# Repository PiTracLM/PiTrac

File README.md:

**Introduction to PiTrac:**

- [Introduction](#introducing-pitrac)
  - [Project Page](#project-page)
- [PiTrac - Start Here](#getting-started)
- [PiTrac - Setup and Configuration](#setup-and-configuration)
- [PiTrac - Licensing](#licensing)
- [PiTrac - Join the Discord](#join-the-discord)

## Introducing PiTrac
Introducing [PiTrac](https://hackaday.io/project/195042-pitrac-the-diy-golf-launch-monitor) \- the world’s first (free\!) open-source golf launch monitor (as far as we know). 

PiTrac uses low-cost Raspberry Pi(\*) computers and cameras to determine golf ball launch speed, angles and spin in three dimensions.  PiTrac interfaces with both GSPro and E6/TruGolf simulators, and its output is also accessible on a stand-alone web-based app.  \[We’ve reached out to 2k/TopGolf, but no response yet.\]

PiTrac uses off-the-shelf hardware, and includes a [parts list](https://docs.pitrac.org/hardware/parts-list/) with links to potential suppliers.  The only custom part is a small printed circuit board.  The fabrication instructions for that PCB are included in the open-source distribution and it can be manufactured for a few dollars.  The two Pi computers and cameras are the most expensive parts, and cost around $250 in total.

PiTrac is not a commercial product for sale–the full design is being released as open source on GitHub for folks to build themselves.  It’s not easy, but if you’re handy with a soldering iron, can figure out how to 3D print the parts, and are willing to burrow into the Linux operating system to compile and install software, you should be able to create your own PiTrac\!  

We are hoping that we can inspire a community of developers to help test and continue PiTrac’s development.  This is a really immature project right now.  The basic features usually work reliably, but the current release is a bit dodgy.  We’re looking for folks to try building their own PiTracs and help us improve the documentation and design to make it easier for other people to do the same.

## Project Page
Please visit our [project page](https://hackaday.io/project/195042-pitrac-the-diy-golf-launch-monitor) and also our YouTube channel [here](https://www.youtube.com/@PiTrac) for more details and videos.  The [GitHub repository](https://github.com/pitraclm/PiTrac) is in the works and already has the 3D printed part designs, the hardware design and initial software documentation.  If you’re interested in more of the details and some of PiTrac’s development history, please look through the [project logs](https://hackaday.io/project/195042-pitrac-the-diy-golf-launch-monitor#menu-logs).  

Finally, any help at our [support page](https://ko-fi.com/Pitrac) would be appreciated to continue this work and complete the release process.

(\*) Raspberry Pi is a trademark of Raspberry Pi Ltd.  The PiTrac project is not endorsed, sponsored by or associated with Raspberry Pi or Raspberry Pi products or services.

## [Getting Started](https://docs.pitrac.org/build-guide/)
The process of building your own PiTrac DIY Launch Monitor is described here at a high level. There are several more-detailed instruction documents elsewhere in the PiTrac repository that are referred to below for various sub-assemblies and tasks like compiling the code and preparing the build environment.

## [Setup and Configuration](https://docs.pitrac.org/software/pi-setup/)
The instructions which are targeted toward getting setup on a step-by-step basis. These instructions start with a Raspberry Pi with nothing on it, and are meant to describe all the steps to get from that point to a working, compiled version of PiTrac.  A single RPi5 is currently our recommended path for everyone, however the path to stereoscopic vision may require two (if/when we head down that path).

## Licensing

PiTrac is distributed under two separate licenses.

The software, documentation, and hardware designs are licensed under the GNU General Public License v2.0. See [`LICENSE`](LICENSE).

PiTrac's trained machine-learning models are not covered by the GPL. They are licensed separately under [`LICENSE.MODEL.md`](LICENSE.MODEL.md), which sets out its own scope and terms. Read it before you use them.

For licensing questions, get in touch through https://github.com/PiTracLM.

## [Join the Discord](https://discord.gg/gMQcBBQYHT)
The PiTrac discord is where you can get help or show off your PiTrac build, discuss features and get to know other PiTrac builders. PiTrac is still a new project, so the Discord is a way to clear up any fuzzy parts of the initial ecosystem. Click the link above or copy this invite link in Discord: `https://discord.gg/gMQcBBQYHT`.

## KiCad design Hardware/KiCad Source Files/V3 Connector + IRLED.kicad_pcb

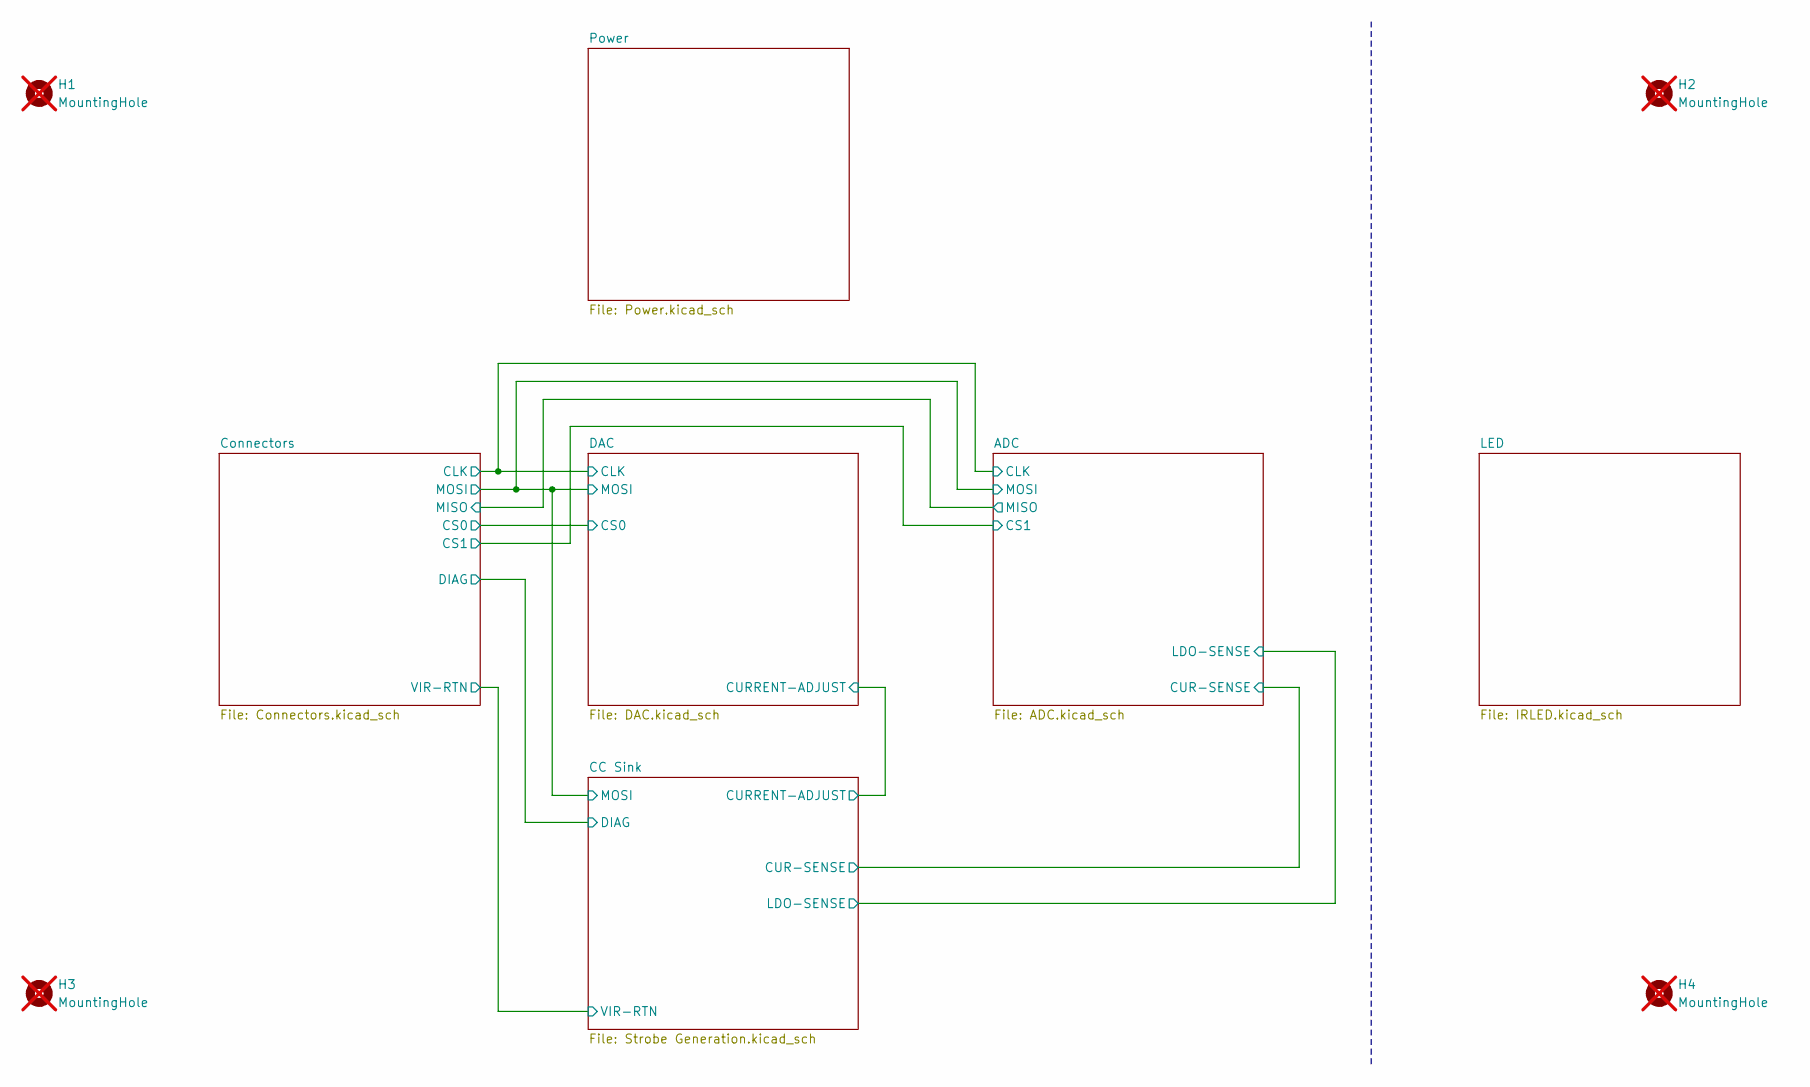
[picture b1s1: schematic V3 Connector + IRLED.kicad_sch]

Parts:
H1, H2, H3, H4: MountingHole; MountingHole_3.5mm; not fitted

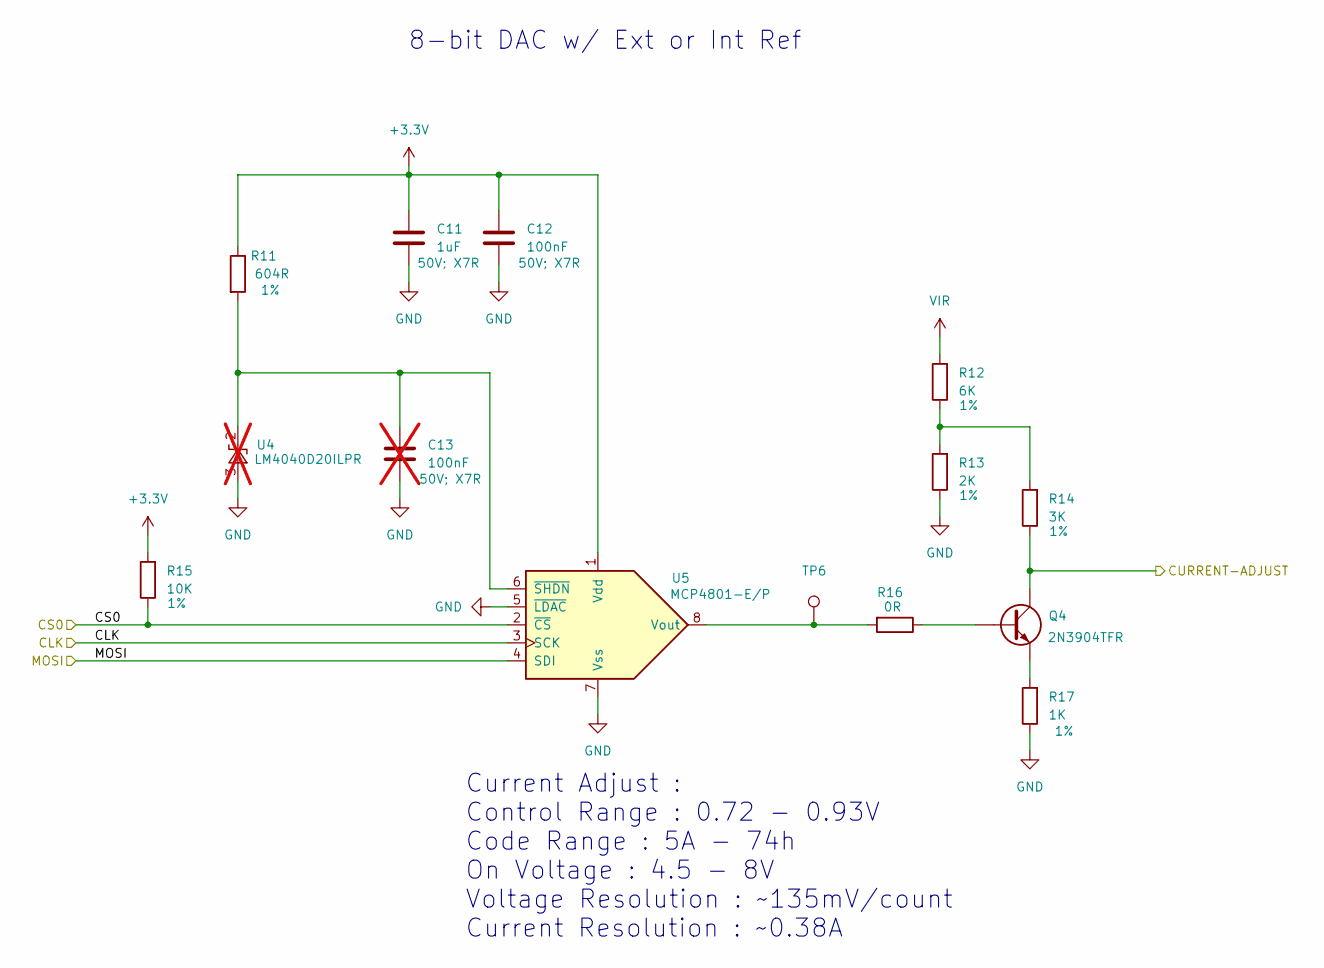
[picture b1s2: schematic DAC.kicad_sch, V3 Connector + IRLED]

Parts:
C11: 1uF; C_Disc_D5.1mm_W3.2mm_P5.00mm; Ratings 50V; X7R; Part Number K105K20X7RF5TH5
C12: 100nF; C_Disc_D4.3mm_W1.9mm_P5.00mm; Ratings 50V; X7R; Part Number K104K10X7RF5UH5
C13: 100nF; C_Disc_D4.3mm_W1.9mm_P5.00mm; Ratings 50V; X7R; Part Number K104K10X7RF5UH5; not fitted
Q4: TO-92_Inline_Wide; Part Number 2N3904TFR
R11: 604R; R_Axial_DIN0207_L6.3mm_D2.5mm_P7.62mm_Horizontal; Ratings 1%; Part Number MFR-25FRF52-604R
R12: 6K; R_Axial_DIN0207_L6.3mm_D2.5mm_P7.62mm_Horizontal; Ratings 1%; Part Number MFR-25FBF52-6K04
R13: 2K; R_Axial_DIN0207_L6.3mm_D2.5mm_P7.62mm_Horizontal; Ratings 1%; Part Number MFR-25FRF52-2K
R14: 3K; R_Axial_DIN0207_L6.3mm_D2.5mm_P7.62mm_Horizontal; Ratings 1%; Part Number MFR-25FRF52-3K
R15: 10K; R_Axial_DIN0207_L6.3mm_D2.5mm_P15.24mm_Horizontal; Ratings 1%; Part Number MFR-25FRF52-10K
R16: 0R; R_Axial_DIN0207_L6.3mm_D2.5mm_P7.62mm_Horizontal; Part Number ZOR-25-R-52-0R
R17: 1K; R_Axial_DIN0207_L6.3mm_D2.5mm_P7.62mm_Horizontal; Ratings 1%; Part Number MFR-25FRF52-1K
TP6: TestPoint; TestPoint_Pad_D1.0mm
U4: LM4040LP-2.0; TO-92_Inline_Wide; Part Number LM4040D20ILPR; not fitted
U5: MCP4801; DIP-8_W7.62mm; Part Number MCP4801-E/P

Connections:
+3.3V: C11.1, C12.1, R11.1, R15.2, U5.1 (Vdd); also elsewhere on the board
/ADC/CLK: U5.3 (SCK); also elsewhere on the board
/ADC/MOSI: U5.4 (SDI); also elsewhere on the board
/CC Sink/CURRENT-ADJUST: Q4.3 (C), R14.1; also elsewhere on the board
/Connectors/CS0: R15.1, U5.2 (~CS); also elsewhere on the board
GND: C11.2, C12.2, C13.2, R13.1, R17.1, U4.3 (A), U5.5 (~LDAC), U5.7 (Vss); also elsewhere on the board
unnamed: Q4.2 (B), R16.1
unnamed: Q4.1 (E), R17.2
unnamed: R12.1, R13.2, R14.2
unnamed: C13.1, R11.2, U4.2 (K), U5.6 (~SHDN)
unnamed: R16.2, TP6.1, U5.8 (Vout)
VIR: R12.2; also elsewhere on the board

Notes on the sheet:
Current Adjust : Control Range : 0.72 - 0.93V Code Range : 5A - 74h On Voltage : 4.5 - 8V Voltage Resolution : ~135mV/count Current Resolution : ~0.38A
8-bit DAC w/ Ext or Int Ref

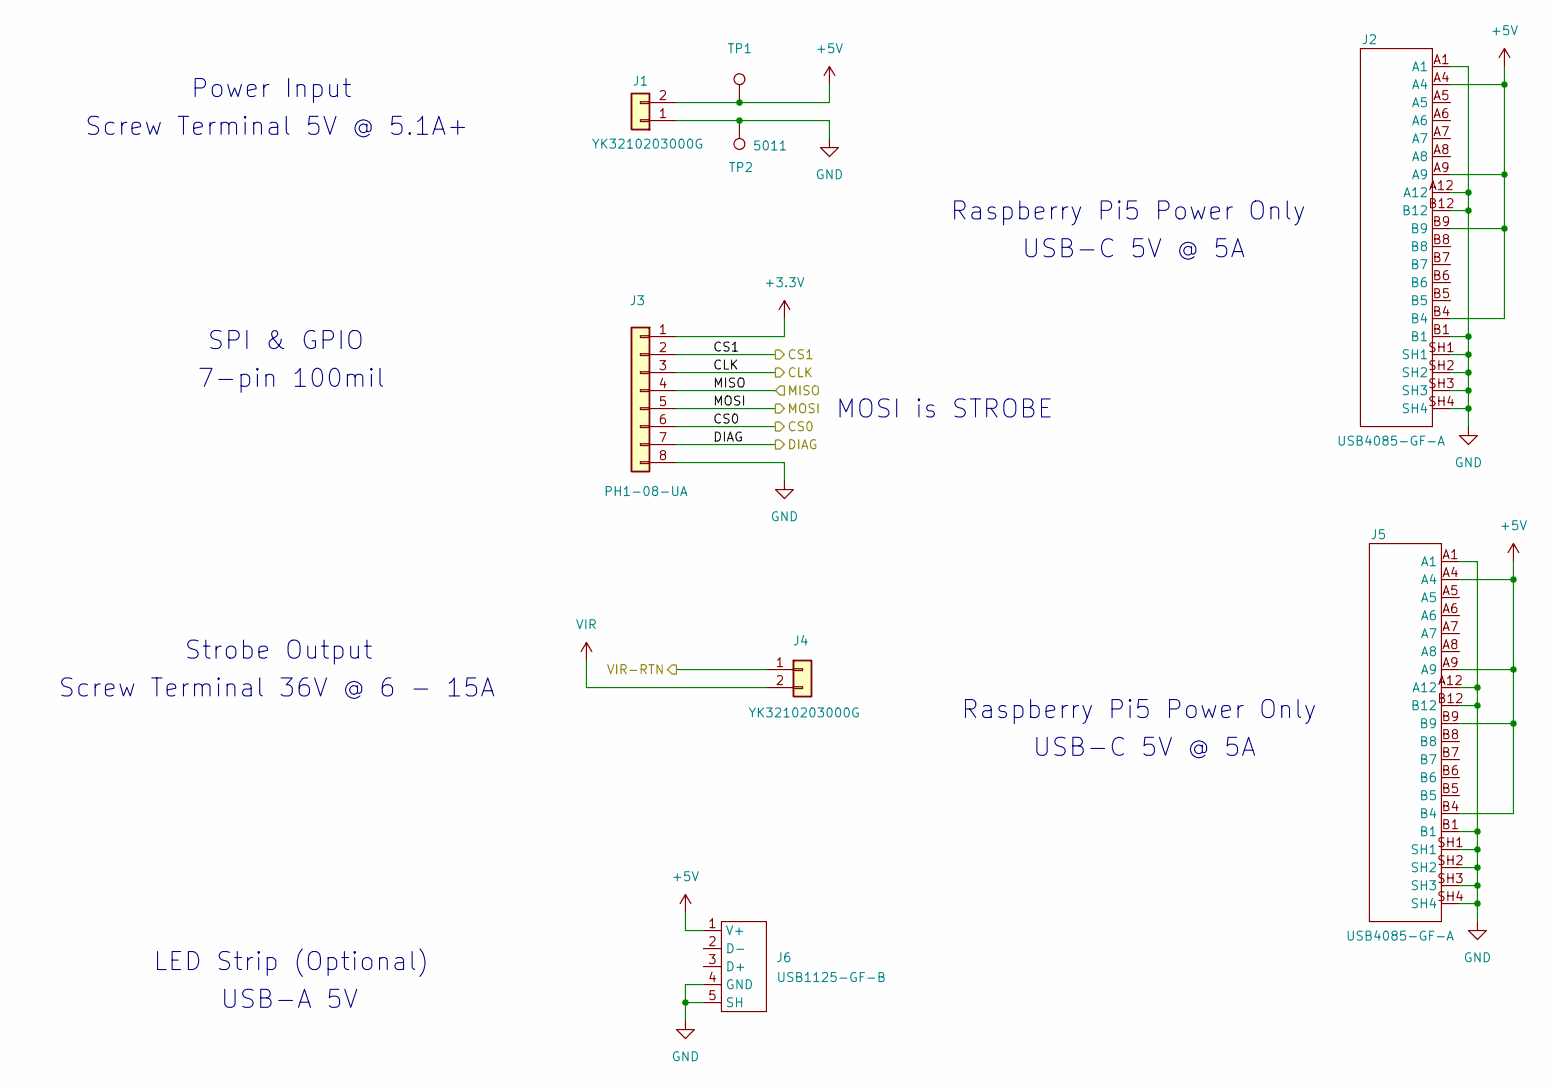
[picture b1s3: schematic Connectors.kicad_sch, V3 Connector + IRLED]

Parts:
J1, J4: YK3210203000G; Part Number YK3210203000G
J2, J5: USB4085-GF-A; Part Number USB4085-GF-A
J3: Conn_01x08; PinHeader_1x08_P2.54mm_Vertical; Part Number PH1-08-UA
J6: USB1125-GF-B; Part Number USB1125-GF-B
TP1: TestPoint; TestPoint_Pad_D1.0mm
TP2: TestPoint; TestPoint_Keystone_5010-5014_Multipurpose; Part Number 5011

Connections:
+3.3V: J3.1; also elsewhere on the board
+5V: J1.2, J2.A4, J2.A9, J2.B4, J2.B9, J5.A4, J5.A9, J5.B4, J5.B9, J6.1 (V+), TP1.1; also elsewhere on the board
/ADC/CLK: J3.3; also elsewhere on the board
/ADC/CS1: J3.2; also elsewhere on the board
/ADC/MISO: J3.4; also elsewhere on the board
/ADC/MOSI: J3.5; also elsewhere on the board
/CC Sink/DIAG: J3.7; also elsewhere on the board
/CC Sink/VIR-RTN: J4.1; also elsewhere on the board
/Connectors/CS0: J3.6; also elsewhere on the board
GND: J1.1, J2.A1, J2.A12, J2.B1, J2.B12, J2.SH1, J2.SH2, J2.SH3, J2.SH4, J3.8, J5.A1, J5.A12, J5.B1, J5.B12, J5.SH1, J5.SH2, J5.SH3, J5.SH4, J6.4 (GND), J6.5 (SH), TP2.1; also elsewhere on the board
VIR: J4.2; also elsewhere on the board

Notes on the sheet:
Power Input
Raspberry Pi5 Power Only
LED Strip (Optional)
Screw Terminal 36V @ 6 - 15A
MOSI is STROBE
7-pin 100mil
USB-C 5V @ 5A
Screw Terminal 5V @ 5.1A+
USB-A 5V
Strobe Output
SPI & GPIO

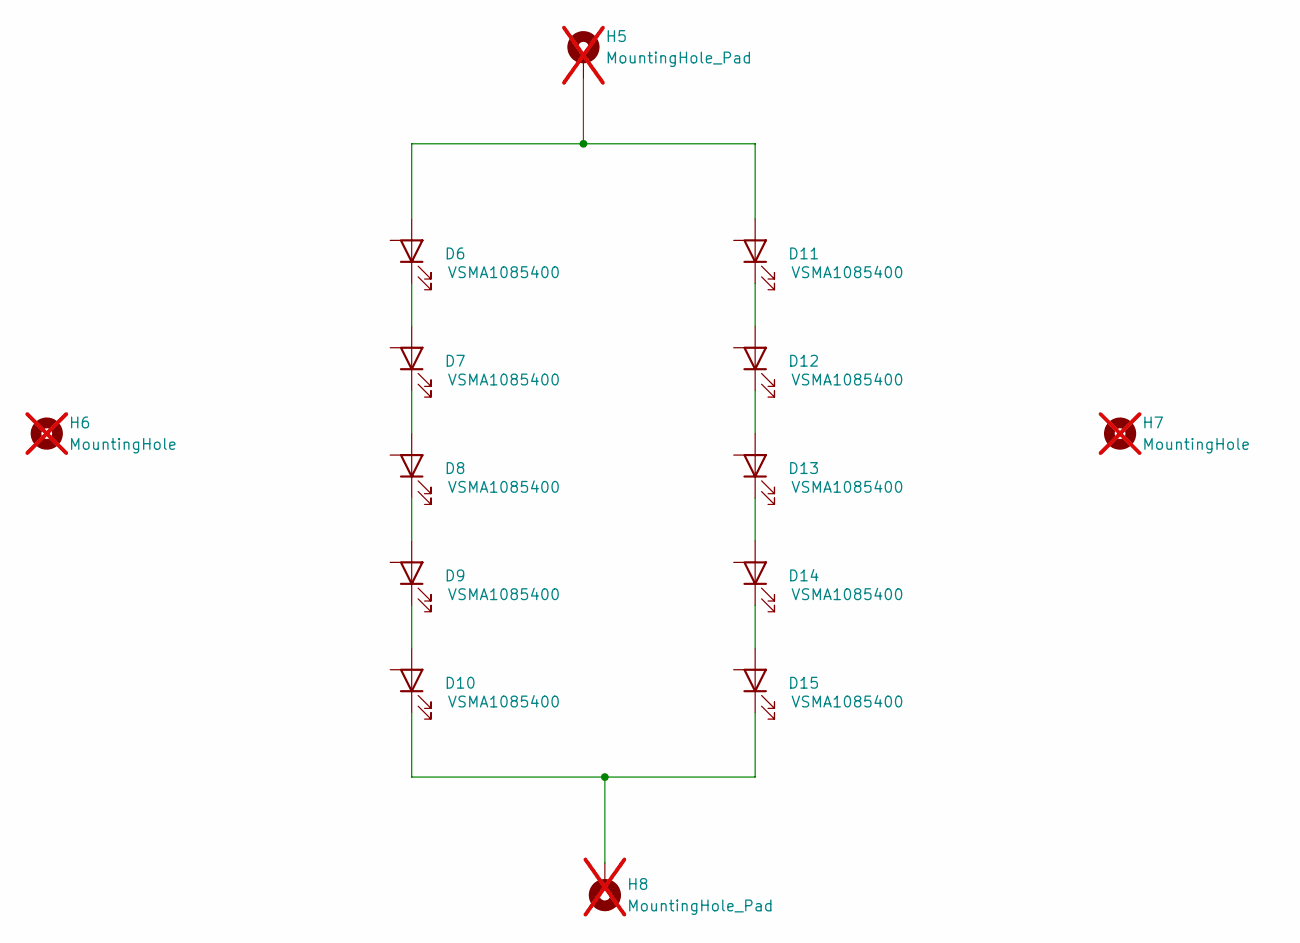
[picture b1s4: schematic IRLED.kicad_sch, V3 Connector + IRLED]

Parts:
D6, D7, D8, D9, D10, D11, D12, D13, D14, D15: VSMA1085400; Part Number VSMA1085400
H5, H8: MountingHole_Pad; MountingHole_2.2mm_M2_Pad; not fitted
H6, H7: MountingHole; MountingHole_3.2mm_M3; not fitted

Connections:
unnamed: D6.1 (K), D7.2 (A)
unnamed: D7.1 (K), D8.2 (A)
unnamed: D8.1 (K), D9.2 (A)
unnamed: D9.1 (K), D10.2 (A)
unnamed: D10.1 (K), D15.1 (K), H8.1
unnamed: D6.2 (A), D11.2 (A), H5.1
unnamed: D11.1 (K), D12.2 (A)
unnamed: D12.1 (K), D13.2 (A)
unnamed: D13.1 (K), D14.2 (A)
unnamed: D14.1 (K), D15.2 (A)

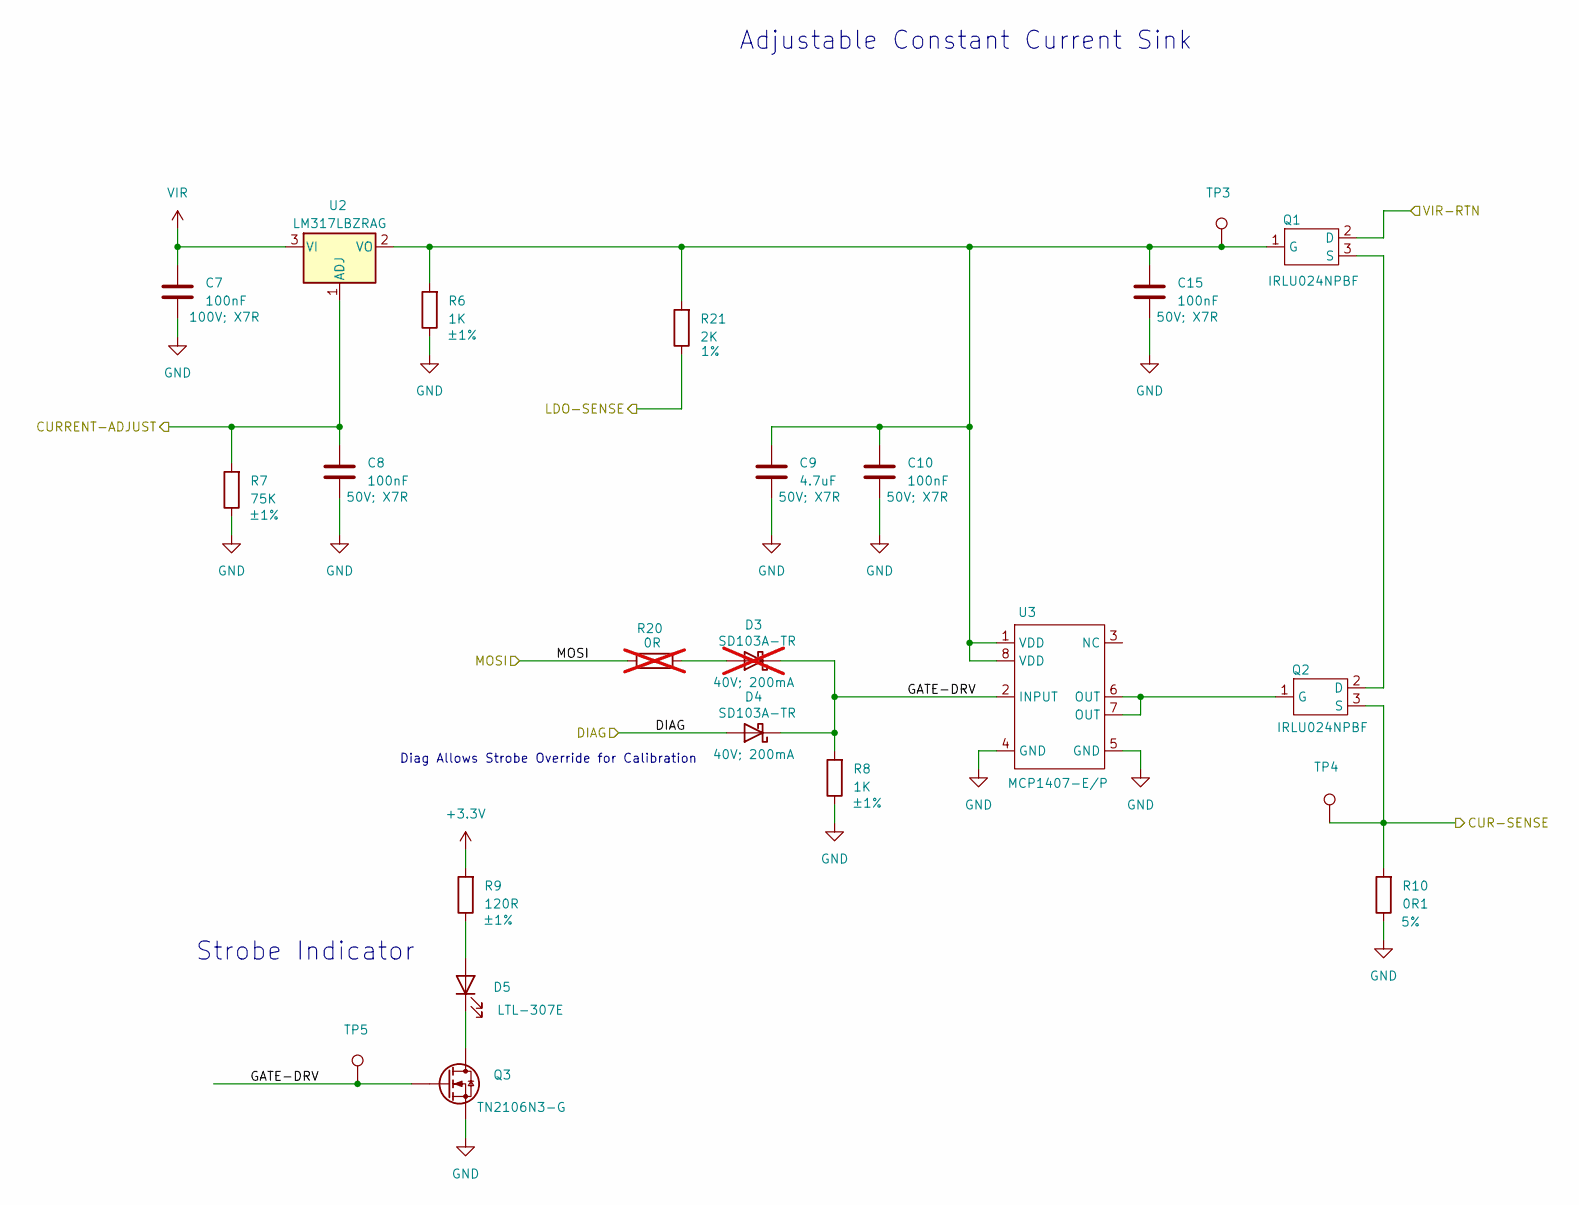
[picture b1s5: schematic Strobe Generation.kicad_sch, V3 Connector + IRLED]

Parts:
C7: 100nF; C_Disc_D5.1mm_W3.2mm_P5.00mm; Ratings 100V; X7R; Part Number K104K20X7RH5UH5
C8, C10, C15: 100nF; C_Disc_D4.3mm_W1.9mm_P5.00mm; Ratings 50V; X7R; Part Number K104K10X7RF5UH5
C9: 4.7uF; C_Disc_D6.0mm_W4.4mm_P5.00mm; Ratings 50V; X7R; Part Number RCER71H475K3K1H03B
D3: D_Schottky; D_DO-35_SOD27_P7.62mm_Horizontal; Ratings 40V; 200mA; Part Number SD103A-TR; not fitted
D4: D_Schottky; D_DO-35_SOD27_P7.62mm_Horizontal; Ratings 40V; 200mA; Part Number SD103A-TR
D5: LTL-307E; LED_D5.0mm; Part Number LTL-307E
Q1, Q2: IRLU024NPBF; TO-251-3_Vertical; Part Number IRLU024NPBF
Q3: Q_NMOS; TO-92_Inline_Wide; Part Number TN2106N3-G
R6, R8: 1K; R_Axial_DIN0207_L6.3mm_D2.5mm_P7.62mm_Horizontal; Ratings ±1%; Part Number MFR-25FRF52-1K
R7: 75K; R_Axial_DIN0207_L6.3mm_D2.5mm_P7.62mm_Horizontal; Ratings ±1%; Part Number MFR-25FRF52-75K
R9: 120R; R_Axial_DIN0207_L6.3mm_D2.5mm_P7.62mm_Horizontal; Ratings ±1%; Part Number MFR-25FTE52-120R
R10: 0R1; R_Axial_DIN0414_L11.9mm_D4.5mm_P15.24mm_Horizontal; Ratings 5%; Part Number KNP100JR-73-0R1
R20: 0R; R_Axial_DIN0207_L6.3mm_D2.5mm_P7.62mm_Horizontal; Part Number ZOR-25-R-52-0R; not fitted
R21: 2K; R_Axial_DIN0207_L6.3mm_D2.5mm_P7.62mm_Horizontal; Ratings 1%; Part Number MFR-25FRF52-2K
TP3, TP4, TP5: TestPoint; TestPoint_Pad_D1.0mm
U2: TO-92_Inline_Wide; Part Number LM317LBZRAG
U3: DIP-8_W7.62mm; Part Number MCP1407-E/P

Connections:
+3.3V: R9.2; also elsewhere on the board
/ADC/CUR-SENSE: Q2.3 (S), R10.2, TP4.1; also elsewhere on the board
/ADC/LDO-SENSE: R21.1; also elsewhere on the board
/ADC/MOSI: R20.2; also elsewhere on the board
/CC Sink/CURRENT-ADJUST: C8.1, R7.2, U2.1 (ADJ); also elsewhere on the board
/CC Sink/DIAG: D4.2 (A); also elsewhere on the board
/CC Sink/GATE-DRV: D3.1 (K), D4.1 (K), Q3.2, R8.2, TP5.1, U3.2 (INPUT)
/CC Sink/VIR-RTN: Q1.2 (D); also elsewhere on the board
GND: C7.2, C8.2, C9.2, C10.2, C15.2, Q3.1, R6.1, R7.1, R8.1, R10.1, U3.4 (GND), U3.5 (GND); also elsewhere on the board
unnamed: D3.2 (A), R20.1
unnamed: D5.2 (A), R9.1
unnamed: D5.1 (K), Q3.3
unnamed: C9.1, C10.1, C15.1, Q1.1 (G), R6.2, R21.2, TP3.1, U2.2 (VO), U3.1 (VDD), U3.8 (VDD)
unnamed: Q1.3 (S), Q2.2 (D)
unnamed: Q2.1 (G), U3.6 (OUT), U3.7 (OUT)
VIR: C7.1, U2.3 (VI); also elsewhere on the board

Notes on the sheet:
Diag Allows Strobe Override for Calibration
Adjustable Constant Current Sink
Strobe Indicator

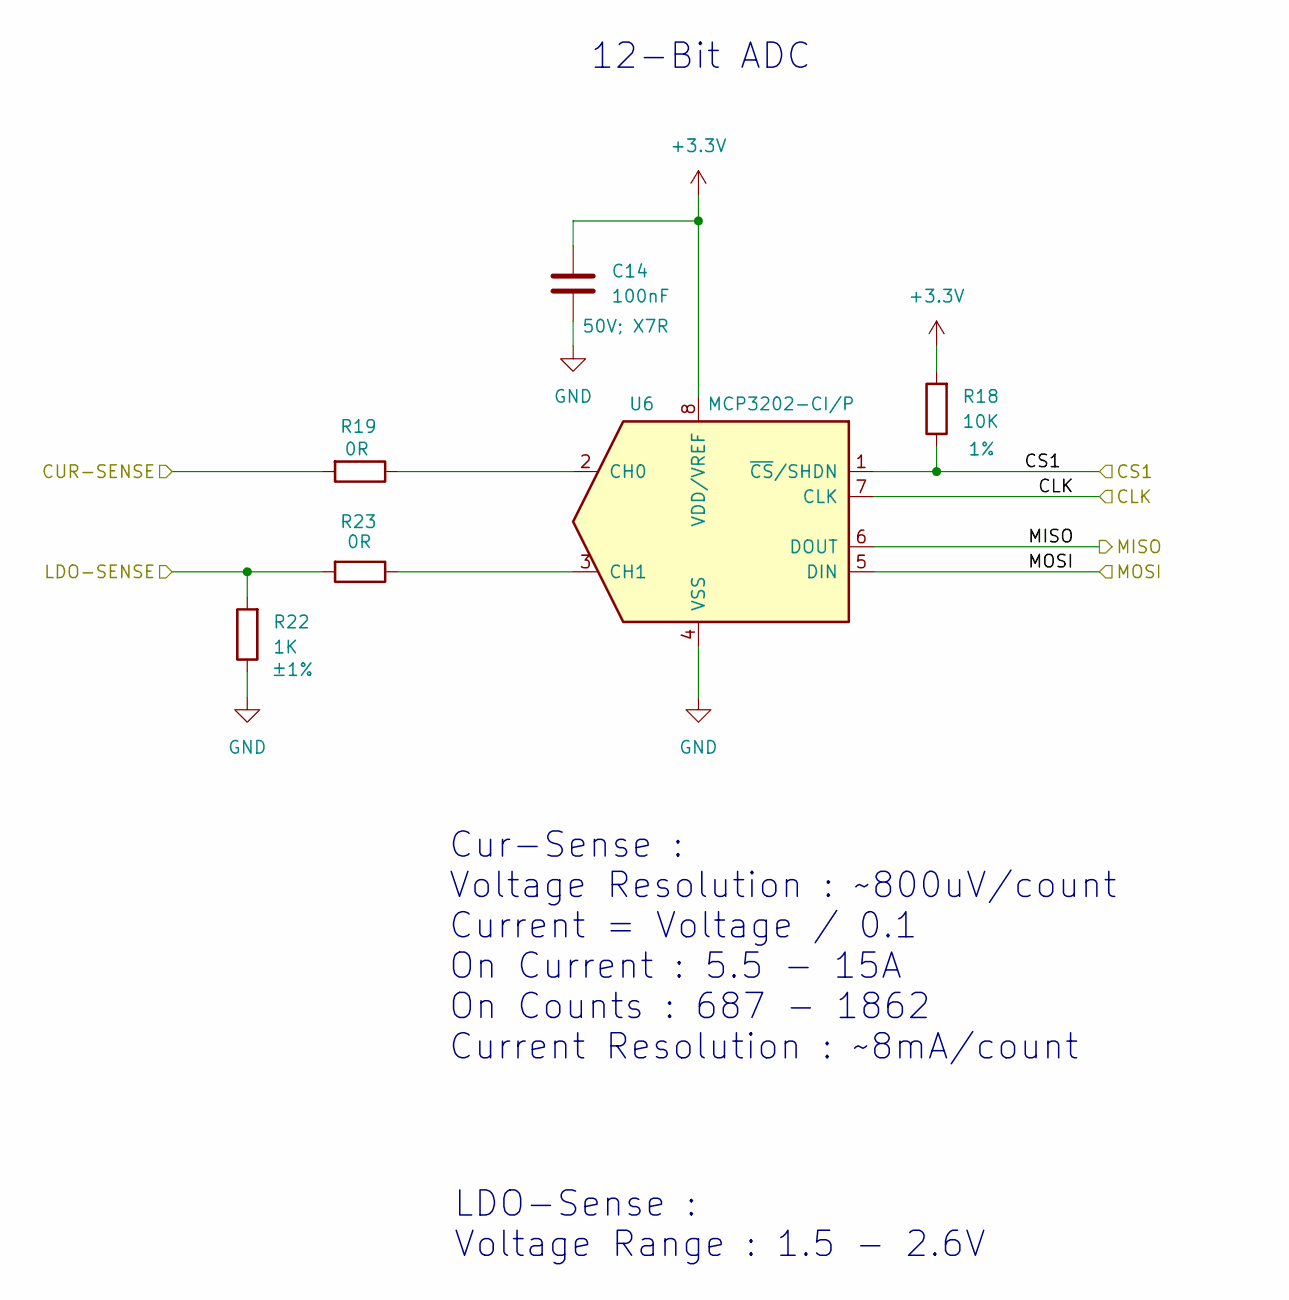
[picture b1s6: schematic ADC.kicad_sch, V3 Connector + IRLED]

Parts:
C14: 100nF; C_Disc_D4.3mm_W1.9mm_P5.00mm; Ratings 50V; X7R; Part Number K104K10X7RF5UH5
R18: 10K; R_Axial_DIN0207_L6.3mm_D2.5mm_P7.62mm_Horizontal; Ratings 1%; Part Number MFR-25FRF52-10K
R19, R23: 0R; R_Axial_DIN0207_L6.3mm_D2.5mm_P15.24mm_Horizontal; Part Number ZOR-25-R-52-0R
R22: 1K; R_Axial_DIN0207_L6.3mm_D2.5mm_P7.62mm_Horizontal; Ratings ±1%; Part Number MFR-25FRF52-1K
U6: MCP3202; DIP-8_W7.62mm; Part Number MCP3202-CI/P

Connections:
+3.3V: C14.1, R18.2, U6.8 (VDD/VREF); also elsewhere on the board
/ADC/CLK: U6.7 (CLK); also elsewhere on the board
/ADC/CS1: R18.1, U6.1 (~CS/SHDN); also elsewhere on the board
/ADC/CUR-SENSE: R19.2; also elsewhere on the board
/ADC/LDO-SENSE: R22.2, R23.2; also elsewhere on the board
/ADC/MISO: U6.6 (DOUT); also elsewhere on the board
/ADC/MOSI: U6.5 (DIN); also elsewhere on the board
GND: C14.2, R22.1, U6.4 (VSS); also elsewhere on the board
unnamed: R19.1, U6.2 (CH0)
unnamed: R23.1, U6.3 (CH1)

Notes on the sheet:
Cur-Sense : Voltage Resolution : ~800uV/count Current = Voltage / 0.1 On Current : 5.5 - 15A On Counts : 687 - 1862 Current Resolution : ~8mA/count
LDO-Sense : Voltage Range : 1.5 - 2.6V
12-Bit ADC

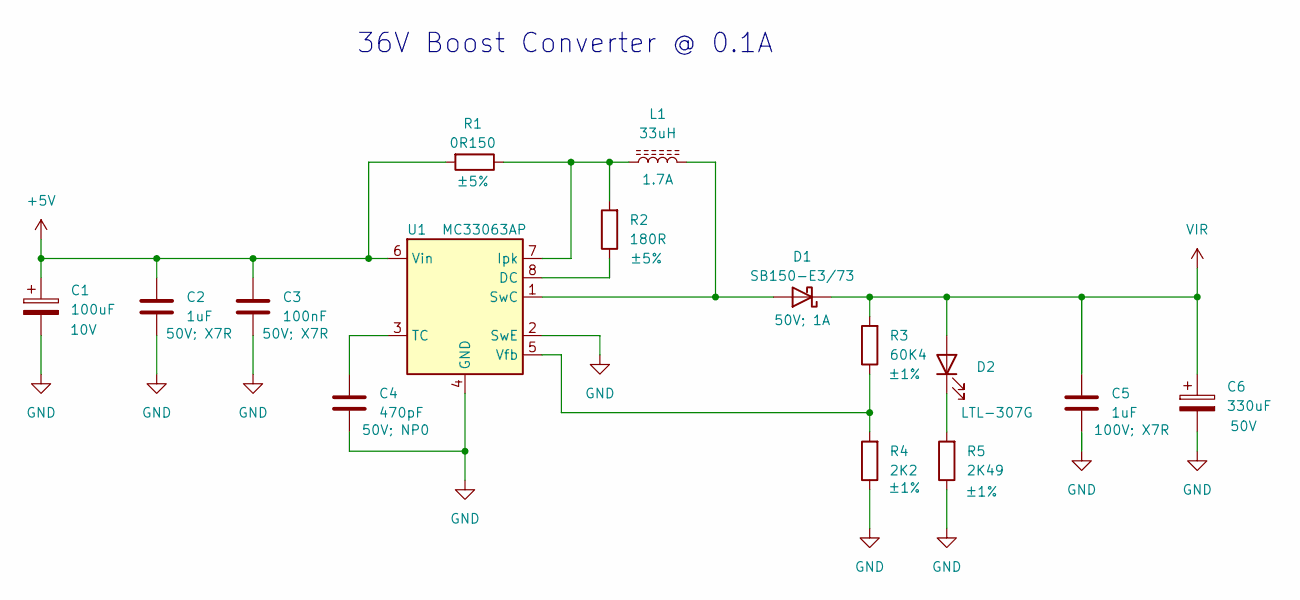
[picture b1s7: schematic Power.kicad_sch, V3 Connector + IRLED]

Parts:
C1: 100uF; CP_Radial_D5.0mm_P2.00mm; Ratings 10V; Part Number A750BK107M1AAAE024
C2: 1uF; C_Disc_D5.1mm_W3.2mm_P5.00mm; Ratings 50V; X7R; Part Number K105K20X7RF5TH5
C3: 100nF; C_Disc_D4.3mm_W1.9mm_P5.00mm; Ratings 50V; X7R; Part Number K104K10X7RF5UH5
C4: 470pF; C_Disc_D4.7mm_W2.5mm_P5.00mm; Ratings 50V; NP0; Part Number K471J15C0GF5UH5
C5: 1uF; C_Disc_D5.1mm_W3.2mm_P5.00mm; Ratings 100V; X7R; Part Number RDER72A105K2M1H03A
C6: 330uF; CP_Radial_D10.0mm_P5.00mm; Ratings 50V; Part Number A750MW337M1HAAE020
D1: SB150-E3/73; D_DO-41_SOD81_P10.16mm_Horizontal; Ratings 50V; 1A; Part Number SB150-E3/73
D2: LTL-307G; LED_D5.0mm; Part Number LTL-307G
L1: 33uH; L_Radial_D8.7mm_P5.00mm_Fastron_07HCP; Ratings 1.7A; Part Number RLB0914-330KL
R1: 0R150; R_Axial_DIN0516_L15.5mm_D5.0mm_P20.32mm_Horizontal; Ratings ±5%; Part Number PNP300JR-73-0R15
R2: 180R; R_Axial_DIN0207_L6.3mm_D2.5mm_P10.16mm_Horizontal; Ratings ±5%; Part Number KNP1WSJT-52-180R
R3: 60K4; R_Axial_DIN0207_L6.3mm_D2.5mm_P7.62mm_Horizontal; Ratings ±1%; Part Number MFR-25FRF52-60K4
R4: 2K2; R_Axial_DIN0207_L6.3mm_D2.5mm_P7.62mm_Horizontal; Ratings ±1%; Part Number MFR-25FRF52-2K2
R5: 2K49; R_Axial_DIN0207_L6.3mm_D2.5mm_P7.62mm_Horizontal; Ratings ±1%; Part Number MFR-25FTE52-2K49
U1: MC33063AP; DIP-8_W7.62mm; Part Number MC33063AP

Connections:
+5V: C1.1, C2.1, C3.1, R1.2, U1.6 (Vin); also elsewhere on the board
GND: C1.2, C2.2, C3.2, C4.1, C5.2, C6.2, R4.1, R5.1, U1.2 (SwE), U1.4 (GND); also elsewhere on the board
unnamed: D1.2 (A), L1.2, U1.1 (SwC)
unnamed: D2.1 (K), R5.2
unnamed: R2.1, U1.8 (DC)
unnamed: L1.1, R1.1, R2.2, U1.7 (Ipk)
unnamed: C4.2, U1.3 (TC)
unnamed: R3.1, R4.2, U1.5 (Vfb)
VIR: C5.1, C6.1, D1.1 (K), D2.2 (A), R3.2; also elsewhere on the board

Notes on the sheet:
36V Boost Converter @ 0.1A

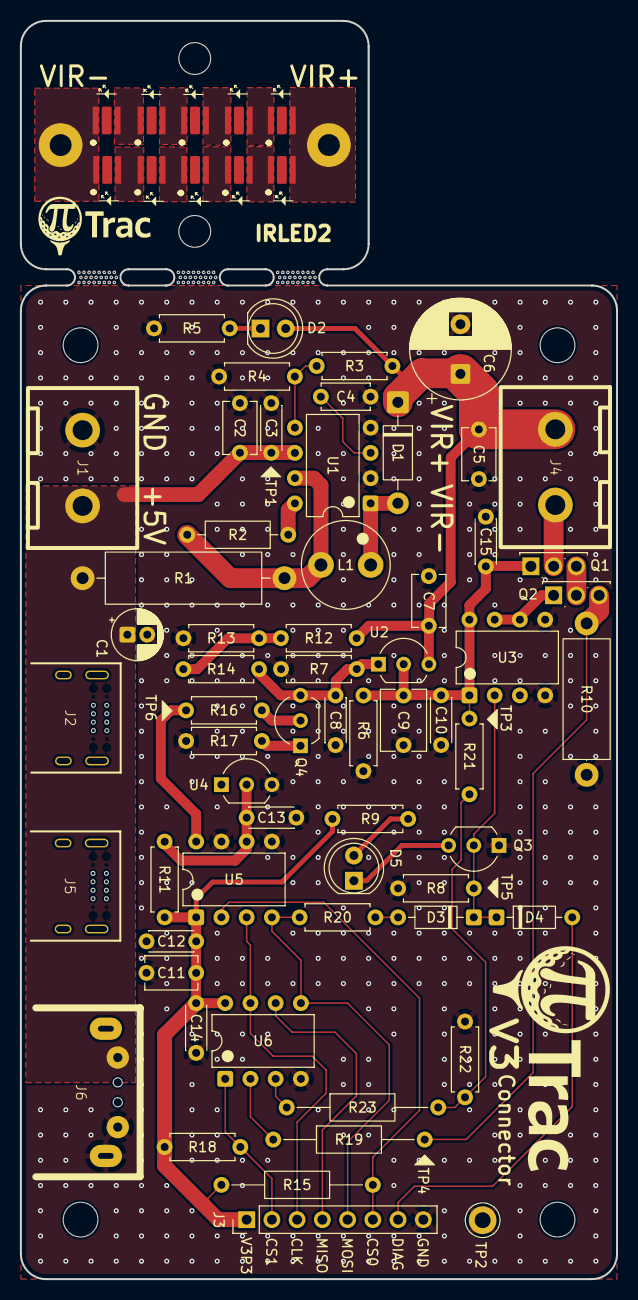
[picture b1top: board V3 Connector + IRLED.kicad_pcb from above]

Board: 2 copper layers, 60.0 x 126.6 mm, 79 parts (0 on the bottom side), 44 nets.

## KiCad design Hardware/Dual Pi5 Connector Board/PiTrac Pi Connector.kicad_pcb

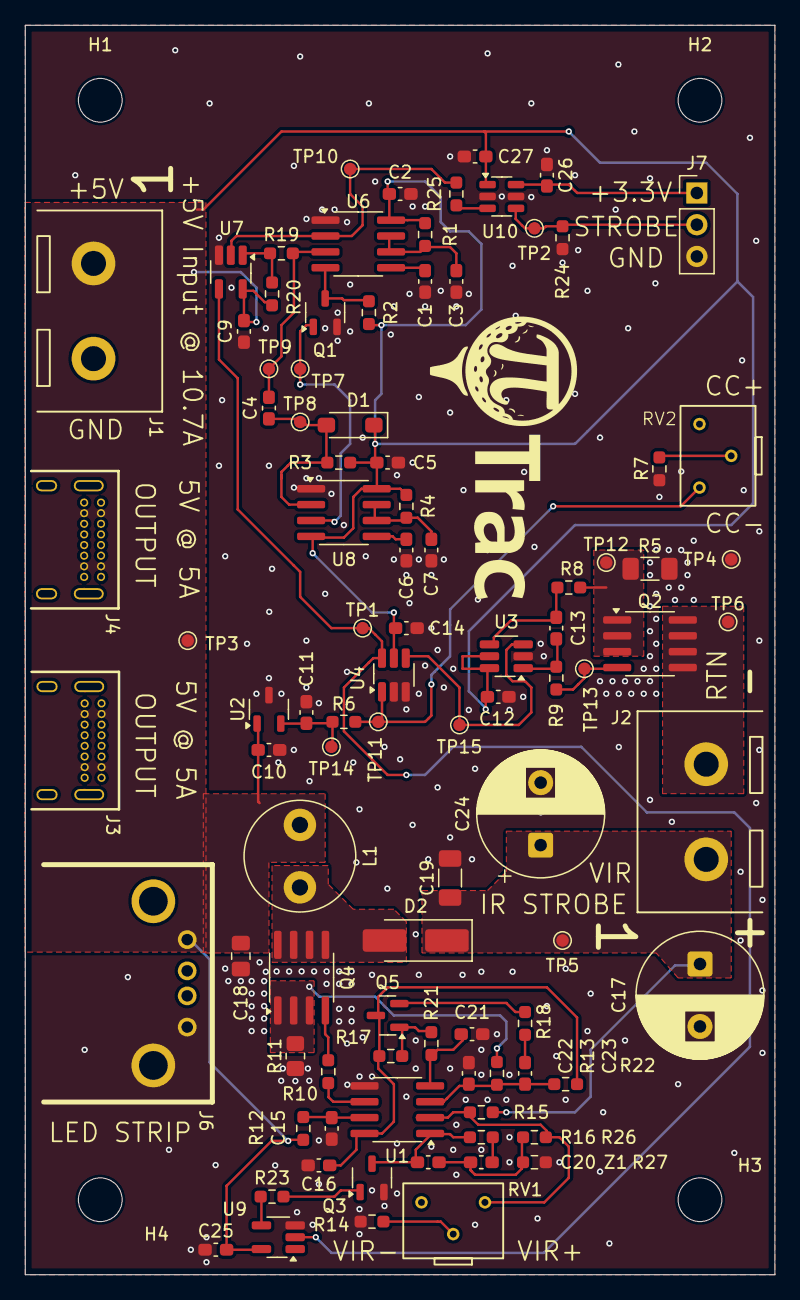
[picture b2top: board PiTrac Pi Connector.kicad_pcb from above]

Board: 2 copper layers, 60.0 x 100.0 mm, 98 parts (0 on the bottom side), 44 nets.

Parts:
C1, C2, C3, C4, C5, C6, C9, C10, C11, C12, C14, C25, C26, C27: 100nF; C_0603_1608Metric_Pad1.08x0.95mm_HandSolder
C7, C15, C16: 1uF; C_0603_1608Metric_Pad1.08x0.95mm_HandSolder
C13, C22: 470pF; C_0603_1608Metric_Pad1.08x0.95mm_HandSolder
C17, C24: 100uF; CP_Radial_D10.0mm_P5.00mm
C18: 4.7uF; C_0805_2012Metric_Pad1.18x1.45mm_HandSolder
C19: 4.7uF; C_1206_3216Metric_Pad1.33x1.80mm_HandSolder
C20: 33pF; C_0603_1608Metric_Pad1.08x0.95mm_HandSolder
C21: 100pF; C_0603_1608Metric_Pad1.08x0.95mm_HandSolder
C23: 10nF; C_0603_1608Metric_Pad1.08x0.95mm_HandSolder
D1: SD103AW-7-F; D_SOD-123_HandSolder
D2: B260AE-13; D_SMA_Handsoldering
H1, H2, H3, H4: MountingHole; MountingHole_3.5mm
J1, J2: YK3210203000G
J3, J4: USB4085-GF-A
J6: USB-A-S-RA
J7: PH1-03-UA; PinHeader_1x03_P2.54mm_Vertical
L1: 33uH; L_Radial_D8.7mm_P5.00mm_Fastron_07HCP
Q1, Q3: DMN6140L-13; SOT-23-3
Q2, Q4: DMT616MLSS-13; SOIC-8_3.9x4.9mm_P1.27mm_HandSolder
Q5: MMBT3904-7-F; SOT-23
R1, R4: 1M; R_0603_1608Metric_Pad0.98x0.95mm_HandSolder
R2, R3, R16, R20, R24: 10k; R_0603_1608Metric_Pad0.98x0.95mm_HandSolder
R5: 33m; R_1206_3216Metric_Pad1.30x1.75mm_HandSolder
R6: 24k; R_0603_1608Metric_Pad0.98x0.95mm_HandSolder
R7: 750; R_0603_1608Metric_Pad0.98x0.95mm_HandSolder
R8: 49.9; R_0603_1608Metric_Pad0.98x0.95mm_HandSolder
R9: 2; R_0603_1608Metric_Pad0.98x0.95mm_HandSolder
R10: 10; R_0603_1608Metric_Pad0.98x0.95mm_HandSolder
R11: 200mOhm; R_0805_2012Metric_Pad1.20x1.40mm_HandSolder
R12, R19, R21, R26, R27: 0; R_0603_1608Metric_Pad0.98x0.95mm_HandSolder
R13: 3.16k; R_0603_1608Metric_Pad0.98x0.95mm_HandSolder
R14: 249; R_0603_1608Metric_Pad0.98x0.95mm_HandSolder
R15: 4.99k; R_0603_1608Metric_Pad0.98x0.95mm_HandSolder
R17: 11k; R_0603_1608Metric_Pad0.98x0.95mm_HandSolder
R18: 24.9k; R_0603_1608Metric_Pad0.98x0.95mm_HandSolder
R22: 13.7k; R_0603_1608Metric_Pad0.98x0.95mm_HandSolder
R23, R25: 27; R_0603_1608Metric_Pad0.98x0.95mm_HandSolder
RV1, RV2: 3362W-1-501LF
TP1, TP2, TP3, TP4, TP5, TP6, TP7, TP8, TP9, TP10, TP11, TP12, TP13, TP14, TP15: TestPoint; TestPoint_Pad_D1.0mm
U1: UCC2813DTR-3; SOIC-8_3.9x4.9mm_P1.27mm_HandSolder
U2: REF3025AIDBZR; SOT-23-3
U3: OPA357AIDBVR; SOT-23-6_Handsoldering
U4: TS5A3157DBVR; SOT-23-6_Handsoldering
U6, U8: TLC555IDR; SOIC-8_3.9x4.9mm_P1.27mm_HandSolder
U7: SN74LVC1G08DBVR; SOT-23-5_HandSoldering
U9: SN74LVC1G17DBVR; SOT-23-5_HandSoldering
U10: SN74LVC1T45DBV; SOT-23-6
Z1: 0R; C_0603_1608Metric_Pad1.08x0.95mm_HandSolder

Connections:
+3.3V: C26.1, J7.1, U10.6 (VCCB)
+5V: C2.1, C5.1, C9.1, C10.1, C12.1, C14.1, C18.1, C25.1, C27.1, D1.1 (K), J1.1, J3.A4, J3.A9, J3.B4, J3.B9, J4.A4, J4.A9, J4.B4, J4.B9, J6.1 (+V), L1.1, R1.1, R2.1, R3.1, R4.1, R12.1, R20.1, TP3.1, U2.1 (VIN), U3.5 (EN), U3.6 (V+), U4.5 (V+), U6.8 (VCC), U7.5 (VCC), U8.4 (R), U8.8 (VCC), U9.5 (VCC), U10.1 (VCCA)
/CC Sink/STROBE-SAFE: TP1.1, U4.6 (IN), U7.4, U9.2
/CC Sink/VIR-RTN: J2.2, Q2.5 (D), Q2.6 (D), Q2.7 (D), Q2.8 (D), TP6.1
/Connectors/STROBE: J7.2, R24.1, TP2.1, U10.4 (B)
GND: C1.2, C2.2, C3.2, C5.2, C6.2, C7.2, C9.2, C10.2, C11.2, C12.2, C14.2, C15.2, C16.2, C17.2, C18.2, C19.2, C21.2, C22.2, C24.2, C25.2, C26.2, C27.2, J1.2, J3.A1, J3.A12, J3.B1, J3.B12, J3.SH1, J3.SH2, J3.SH3, J3.SH4, J4.A1, J4.A12, J4.B1, J4.B12, J4.SH1, J4.SH2, J4.SH3, J4.SH4, J6.4 (GND), J6.SH1, J6.SH2, J7.3, Q1.2, Q3.2, R5.2, R7.1, R11.1, R14.1, R24.2, R27.1, TP4.1, U1.5 (GND), U2.3 (GND), U3.2 (V-), U4.2 (GND), U4.3 (NC), U6.1 (GND), U7.3 (GND), U8.1 (GND), U9.3 (GND), U10.2 (GND), U10.5 (DIR)
unnamed: C13.2, R9.2, U3.1
unnamed: C20.2, R26.1, R27.2, Z1.2
unnamed: C23.1, R18.1
unnamed: C4.2, D1.2 (A), R3.2, TP8.1, U8.2 (TR)
unnamed: D2.2 (A), L1.2, Q4.5 (D), Q4.6 (D), Q4.7 (D), Q4.8 (D)
unnamed: Q2.4 (G), R9.1, TP13.1
unnamed: Q2.1 (S), Q2.2 (S), Q2.3 (S), R5.1, R8.1, TP12.1
unnamed: Q3.1, R23.2
unnamed: Q4.4 (G), R10.2
unnamed: Q4.1 (S), Q4.2 (S), Q4.3 (S), R11.2, R13.2
unnamed: Q5.1 (B), R17.1, R21.2
unnamed: C16.1, Q5.3 (C), R17.2, R22.2, U1.8 (REF)
unnamed: Q5.2 (E), R18.2
unnamed: R7.2, RV2.2
unnamed: R14.2, RV1.2
unnamed: R16.1, Z1.1
unnamed: R19.2, R20.2, U7.1
unnamed: R23.1, U9.4
unnamed: C20.1, Q3.3, R16.2, U1.1 (COMP)
unnamed: C22.1, C23.2, R13.1, R22.1, U1.3 (CS)
unnamed: R15.1, R26.2, RV1.1, U1.2 (FB)
unnamed: R10.1, U1.6 (OUT)
unnamed: C21.1, R21.1, U1.4 (RC)
unnamed: C15.1, R12.2, U1.7 (VCC)
unnamed: C11.1, R6.1, TP14.1, U2.2 (VOUT)
unnamed: TP15.1, U3.3 (+), U4.4 (COM)
unnamed: C13.1, R8.2, U3.4 (-)
unnamed: R6.2, RV2.3, TP11.1, U4.1 (NO)
unnamed: C1.1, U6.5 (CV)
unnamed: C3.1, R1.2, U6.6 (THR), U6.7 (DIS)
unnamed: C4.1, R19.1, TP9.1, U6.3 (Q)
unnamed: Q1.3, R2.2, U6.4 (R)
unnamed: R25.2, TP10.1, U6.2 (TR), U7.2
unnamed: C6.1, U8.5 (CV)
unnamed: C7.1, R4.2, U8.6 (THR), U8.7 (DIS)
unnamed: Q1.1, TP7.1, U8.3 (Q)
unnamed: R25.1, U10.3 (A)
VIR: C17.1, C19.1, C24.1, D2.1 (K), J2.1, R15.2, TP5.1
